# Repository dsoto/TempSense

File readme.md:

# TempSense Temperature Sensor

The first goal of the project is to provide a convenient and cost-effective logger for temperature observations in classrooms or laboratories.
The second goal of the project is to create an accessible introduction to scientific instruments and visualization through a highly-scaffolded open source hardware/software project.

This repository contains the specifications and schematics for the hardware, software to log temperatures, and potential lessons for students.

The hardware in this project is licensed under CERN-OHL-P v2.

The software in this project is licensed under MIT.

The documentation in this project is licensed under CC-BY 4.0.

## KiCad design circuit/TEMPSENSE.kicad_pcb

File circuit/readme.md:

# TempSense Temperature Logger

This is a simple multi-channel temperature logger board and real-time display application.

This folder contains the circuit schematic and board layout files in KiCad format.

# License

This software is released under the CERN-OHL-P v2 license.

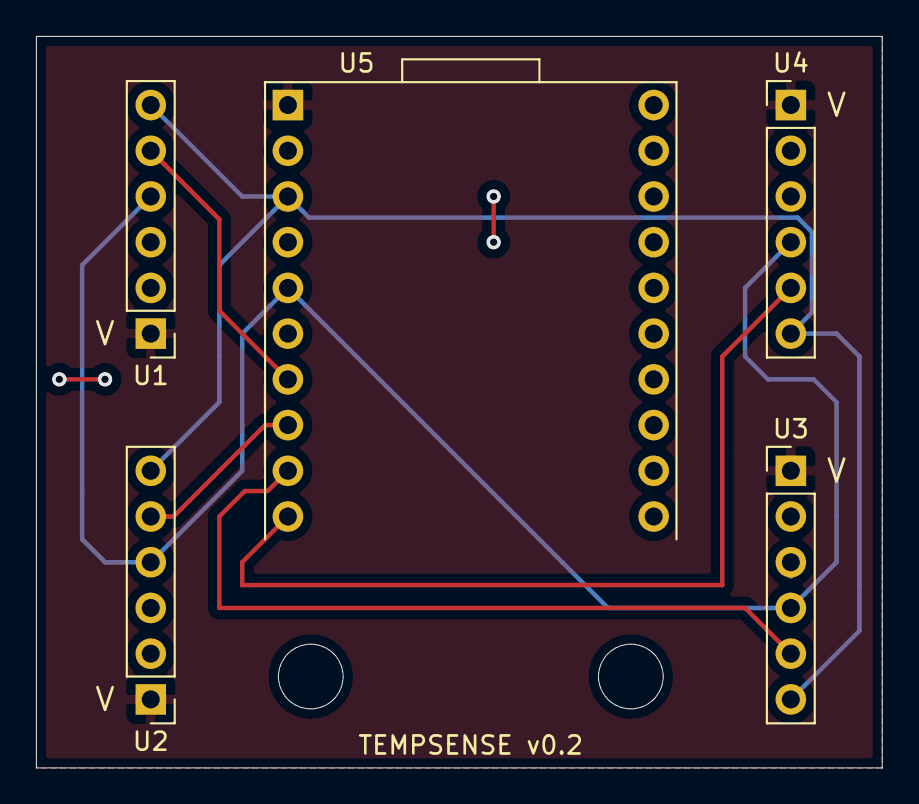
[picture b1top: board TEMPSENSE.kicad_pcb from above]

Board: 2 copper layers, 47.0 x 40.6 mm, 5 parts (0 on the bottom side), 8 nets.

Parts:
U1, U2, U3, U4: MAX31855; Max-31855-board
U5: FT232H; FT232H-socket

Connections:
+5V: U1.1, U2.1, U3.1, U4.1, U5.1
CIPO: U1.4, U2.4, U3.4, U4.4, U5.5
CLK: U1.6, U2.6, U3.6, U4.6, U5.3
GND: U1.3, U2.3, U3.3, U4.3, U5.2
unnamed: U1.5, U5.7
unnamed: U2.5, U5.8
unnamed: U3.5, U5.9
unnamed: U4.5, U5.10

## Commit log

2020-07-08 adds readme
2020-07-08 adds software folder
2020-07-08 adds lesson folder
2020-07-08 reduce image sizes
2020-07-14 adds ideas for second and third lesson
2020-07-15 adds file that calls a single sensor and prints to screen
2020-07-16 update comments
2020-07-16 adds code with four sensor readings
2020-08-24 adds circuit files
2020-09-16 screenshot from this version
2020-09-21 updates schematic and pcb
2020-09-21 removes unused programs
2020-09-21 updates legend location
2020-09-21 adds shell scripts for launch
2020-09-21 edits to enhance readability
2020-09-22 adds environment file
2020-09-24 makes changes in script for windows
2020-09-24 adds text output file
2020-09-24 adds test of CRLF line endings
2020-09-24 removes blank lines from CRLF test file
2020-10-08 updates scripts
2020-10-08 updates images and readme files
2020-10-08 add PDF schematic
2020-10-08 changes filenames to camel case
2020-10-12 adds alternate activate commands
2020-10-29 adds instructions
2020-10-29 adds description
2020-10-29 moves instructions file
2020-10-29 updates figure links
2020-10-29 adds calibration and future work sections
2020-10-29 adds reference list
2020-10-29 adds figures, removes fig refs
2020-11-09 adds bill of materials
2020-11-17 change plot labels and add figure title
2021-03-30 adds license information to files
2021-03-30 adds link to OSHPark
2021-04-07 uses short MIT headers
2021-04-07 change folder name to hardware
2021-04-07 adds title
